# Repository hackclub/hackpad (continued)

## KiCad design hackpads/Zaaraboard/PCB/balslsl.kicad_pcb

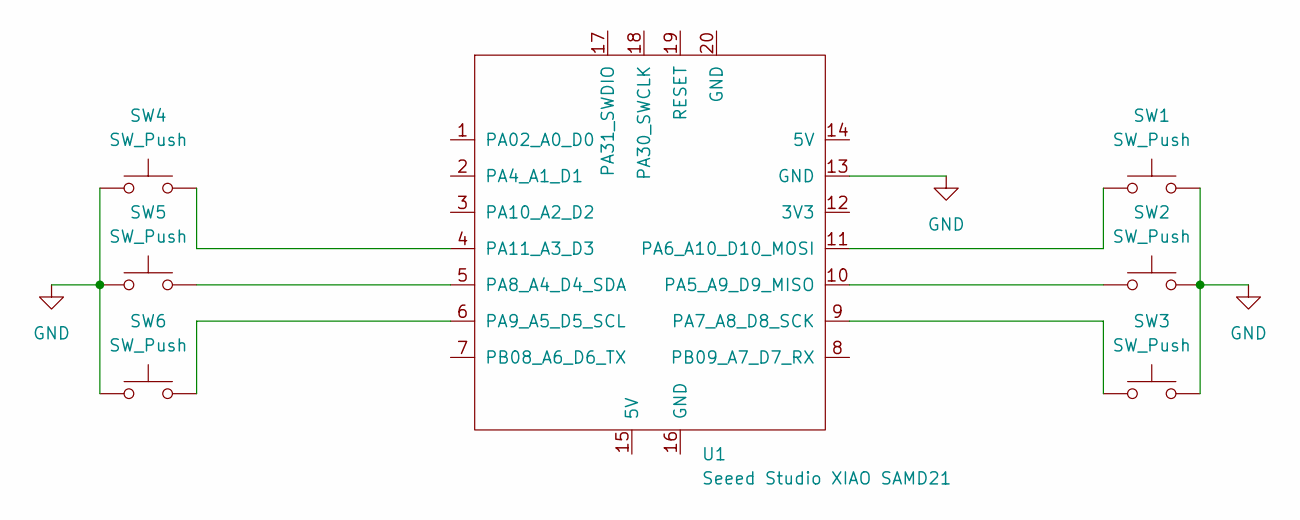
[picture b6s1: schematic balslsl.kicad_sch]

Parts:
SW1, SW2, SW3, SW4, SW5, SW6: SW_Push; SW_Cherry_MX_1.00u_PCB
U1: Seeed Studio XIAO SAMD21; XIAO-Generic-Thruhole-14P-2.54-21X17.8MM

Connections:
GND: SW1.2, SW2.2, SW3.2, SW4.2, SW5.2, SW6.2, U1.2 (PA4_A1_D1), U1.13 (GND)
unnamed: SW2.1, U1.10 (PA5_A9_D9_MISO)
unnamed: SW1.1, U1.11 (PA6_A10_D10_MOSI)
unnamed: SW3.1, U1.9 (PA7_A8_D8_SCK)
unnamed: SW5.1, U1.5 (PA8_A4_D4_SDA)
unnamed: SW6.1, U1.6 (PA9_A5_D5_SCL)
unnamed: SW4.1, U1.4 (PA11_A3_D3)

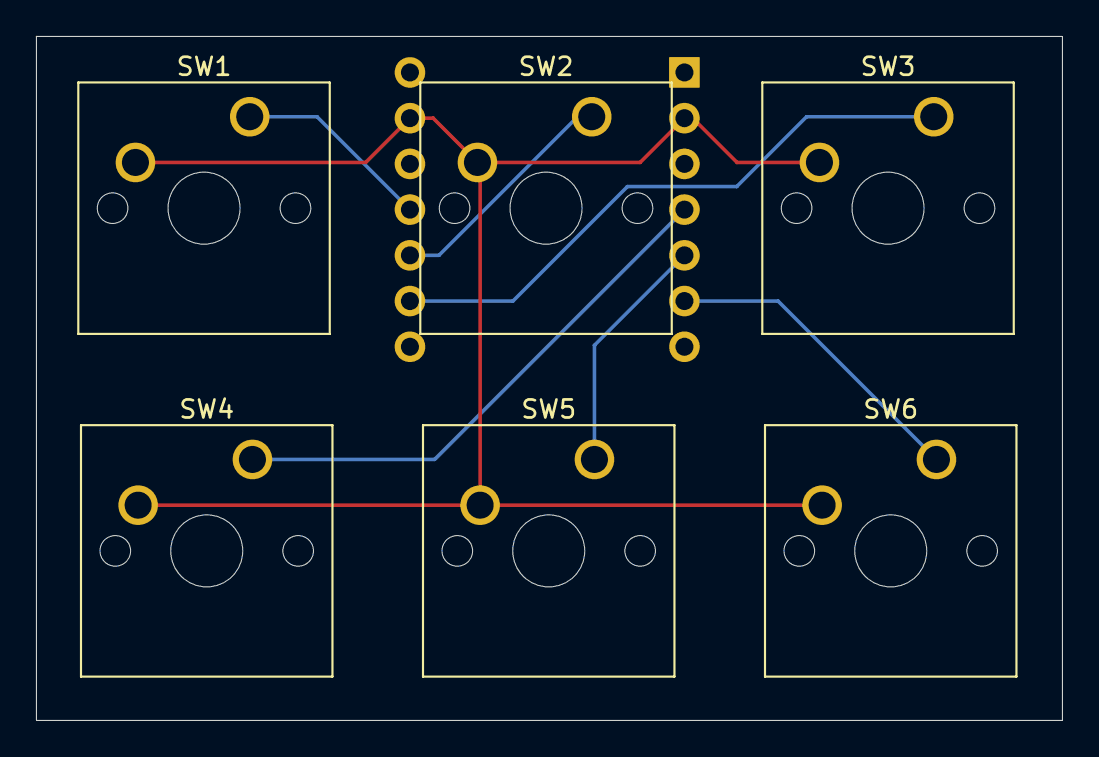
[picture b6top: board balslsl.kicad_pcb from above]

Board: 2 copper layers, 57.0 x 38.0 mm, 7 parts (1 on the bottom side), 7 nets.

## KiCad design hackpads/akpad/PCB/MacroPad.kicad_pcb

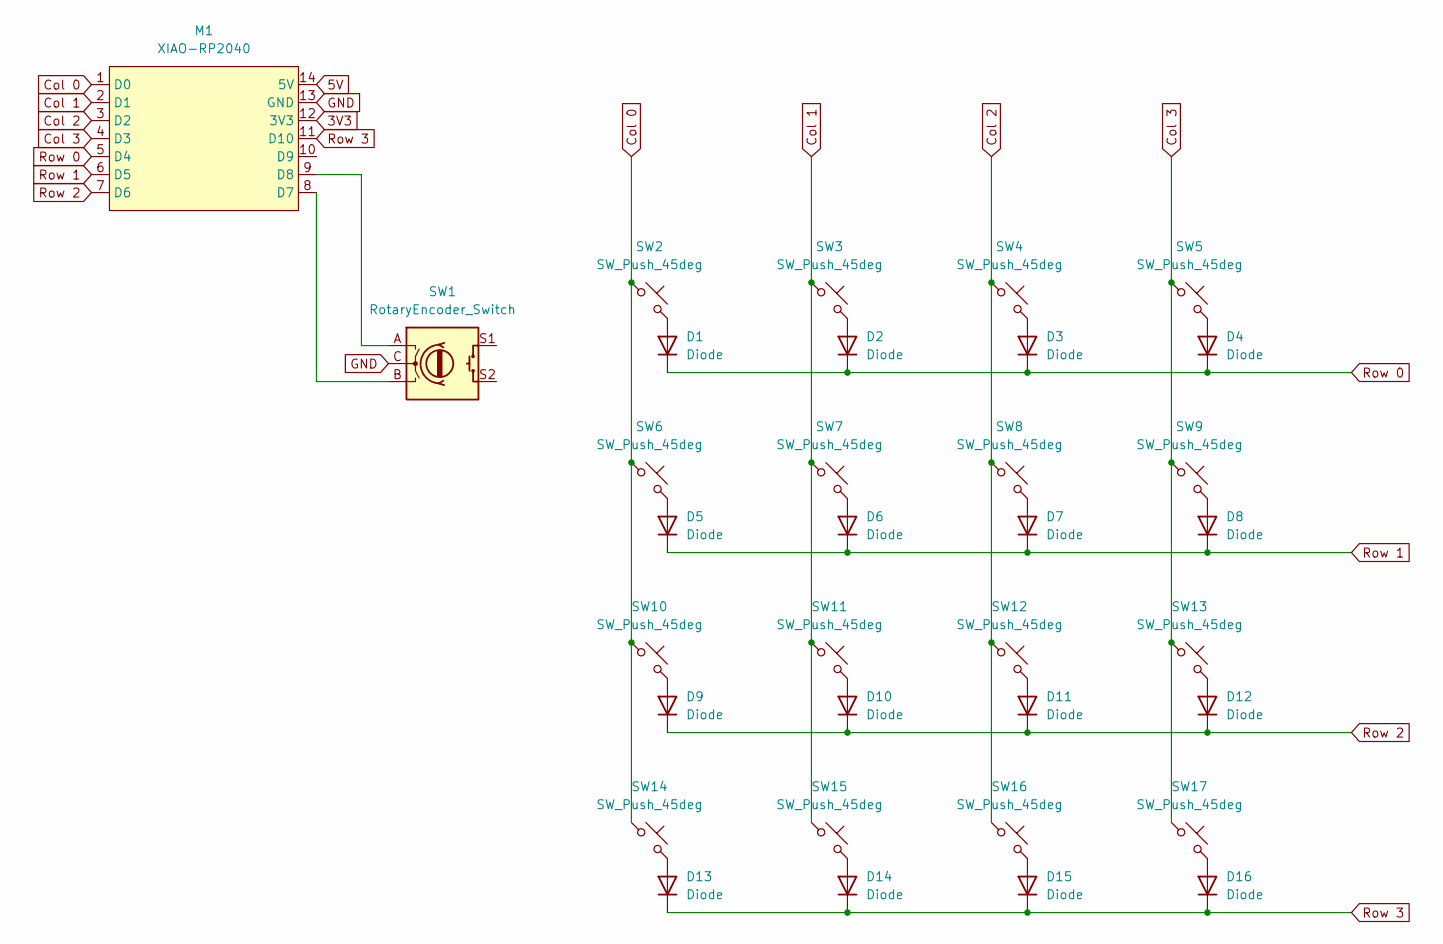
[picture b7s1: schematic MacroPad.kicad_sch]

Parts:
D1, D2, D3, D4, D5, D6, D7, D8, D9, D10, D11, D12, D13, D14, D15, D16: Diode; D_DO-35_SOD27_P7.62mm_Horizontal
M1: XIAO-RP2040; Seeed_XIAO_RP2040
SW1: RotaryEncoder_Switch; RotaryEncoder_Alps_EC11E-Switch_Vertical_H20mm
SW2, SW3, SW4, SW5, SW6, SW7, SW8, SW9, SW10, SW11, SW12, SW13, SW14, SW15, SW16, SW17: SW_Push_45deg; MX_PCB_1.00u

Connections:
3V3: M1.12 (3V3)
5V: M1.14 (5V)
Col 0: M1.1 (D0), SW2.1, SW6.1, SW10.1, SW14.1
Col 1: M1.2 (D1), SW3.1, SW7.1, SW11.1, SW15.1
Col 2: M1.3 (D2), SW4.1, SW8.1, SW12.1, SW16.1
Col 3: M1.4 (D3), SW5.1, SW9.1, SW13.1, SW17.1
GND: M1.13 (GND), SW1.C
unnamed: D1.2 (A), SW2.2
unnamed: D2.2 (A), SW3.2
unnamed: D3.2 (A), SW4.2
unnamed: D4.2 (A), SW5.2
unnamed: D5.2 (A), SW6.2
unnamed: D6.2 (A), SW7.2
unnamed: D7.2 (A), SW8.2
unnamed: D8.2 (A), SW9.2
unnamed: D9.2 (A), SW10.2
unnamed: D10.2 (A), SW11.2
unnamed: D11.2 (A), SW12.2
unnamed: D12.2 (A), SW13.2
unnamed: D13.2 (A), SW14.2
unnamed: D14.2 (A), SW15.2
unnamed: D15.2 (A), SW16.2
unnamed: D16.2 (A), SW17.2
unnamed: M1.8 (D7), SW1.B
unnamed: M1.9 (D8), SW1.A
Row 0: D1.1 (K), D2.1 (K), D3.1 (K), D4.1 (K), M1.5 (D4)
Row 1: D5.1 (K), D6.1 (K), D7.1 (K), D8.1 (K), M1.6 (D5)
Row 2: D9.1 (K), D10.1 (K), D11.1 (K), D12.1 (K), M1.7 (D6)
Row 3: D13.1 (K), D14.1 (K), D15.1 (K), D16.1 (K), M1.11 (D10)

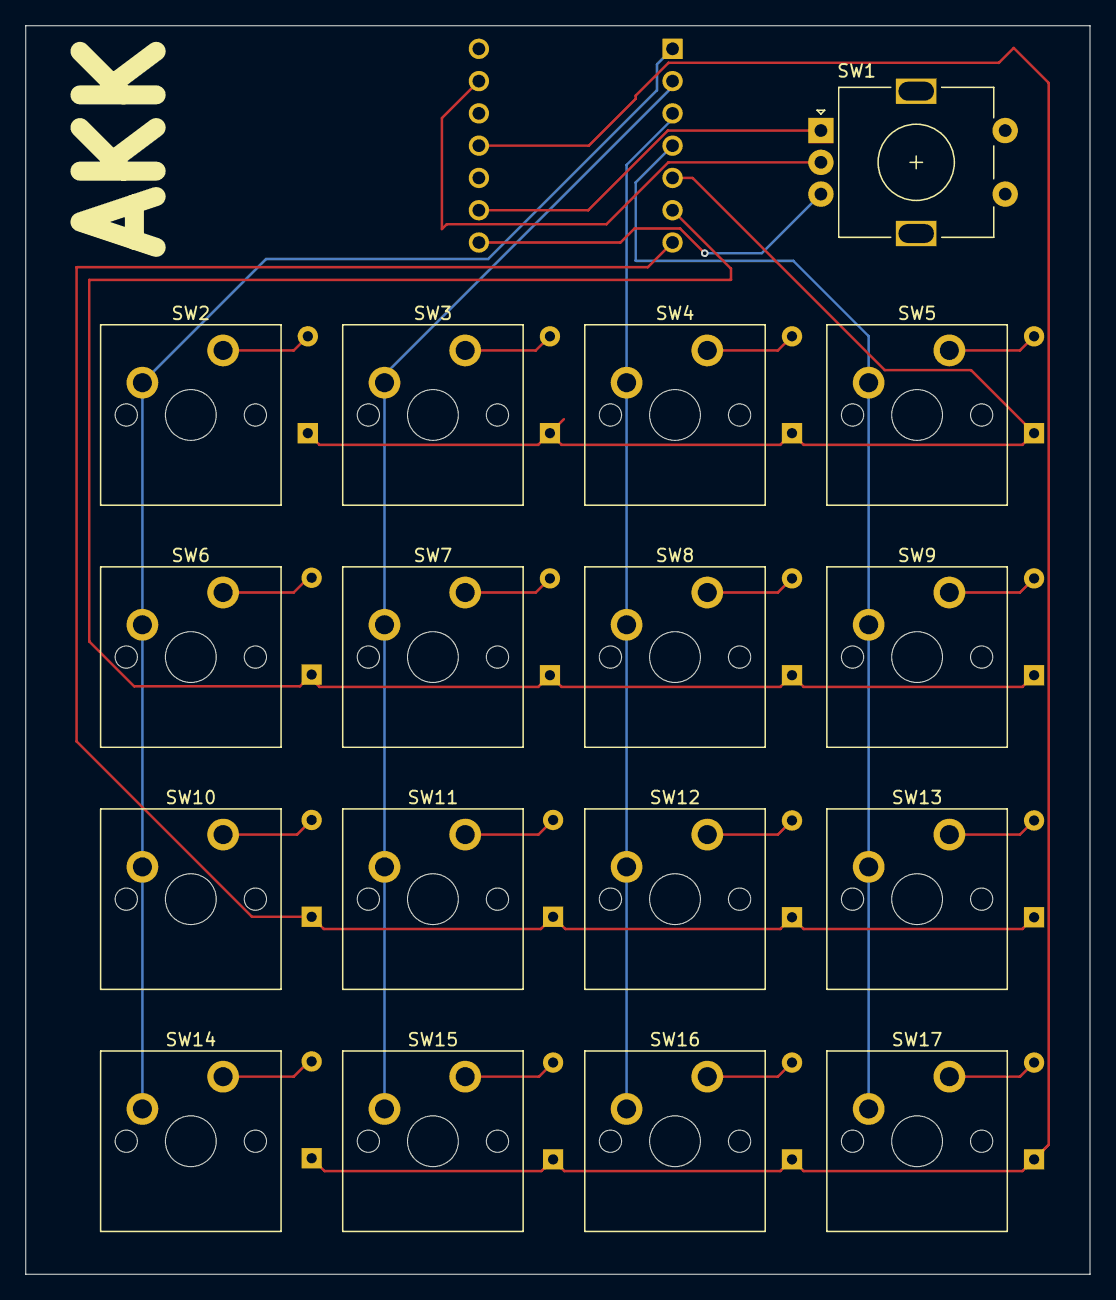
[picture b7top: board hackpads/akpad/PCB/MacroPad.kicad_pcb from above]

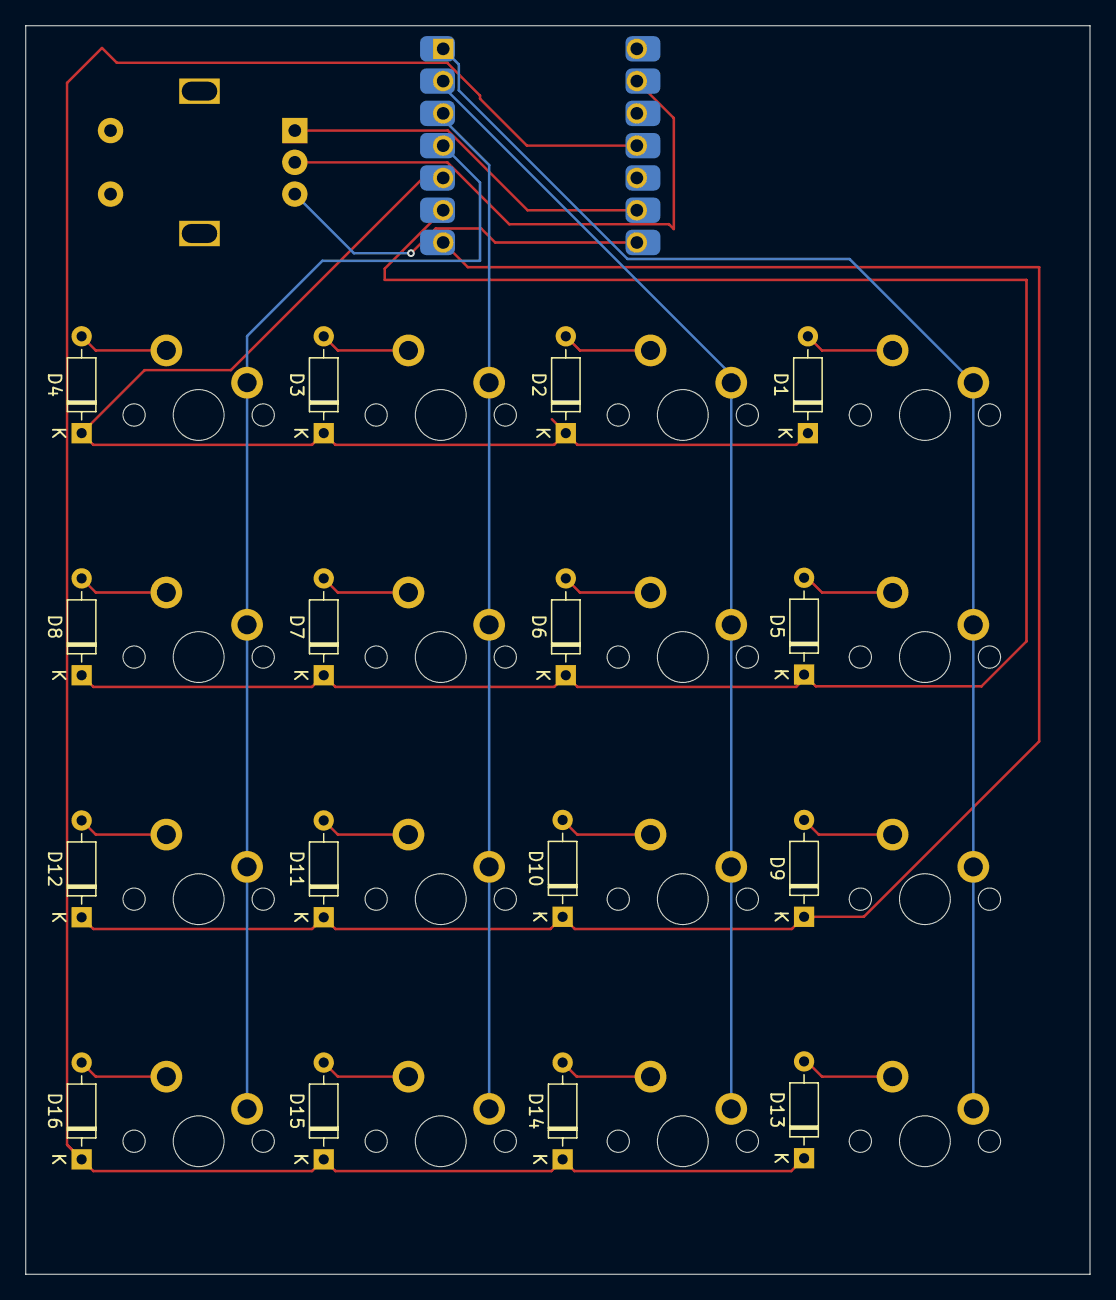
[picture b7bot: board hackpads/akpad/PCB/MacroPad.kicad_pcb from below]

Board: 2 copper layers, 83.8 x 98.2 mm, 34 parts (17 on the bottom side), 27 nets.
